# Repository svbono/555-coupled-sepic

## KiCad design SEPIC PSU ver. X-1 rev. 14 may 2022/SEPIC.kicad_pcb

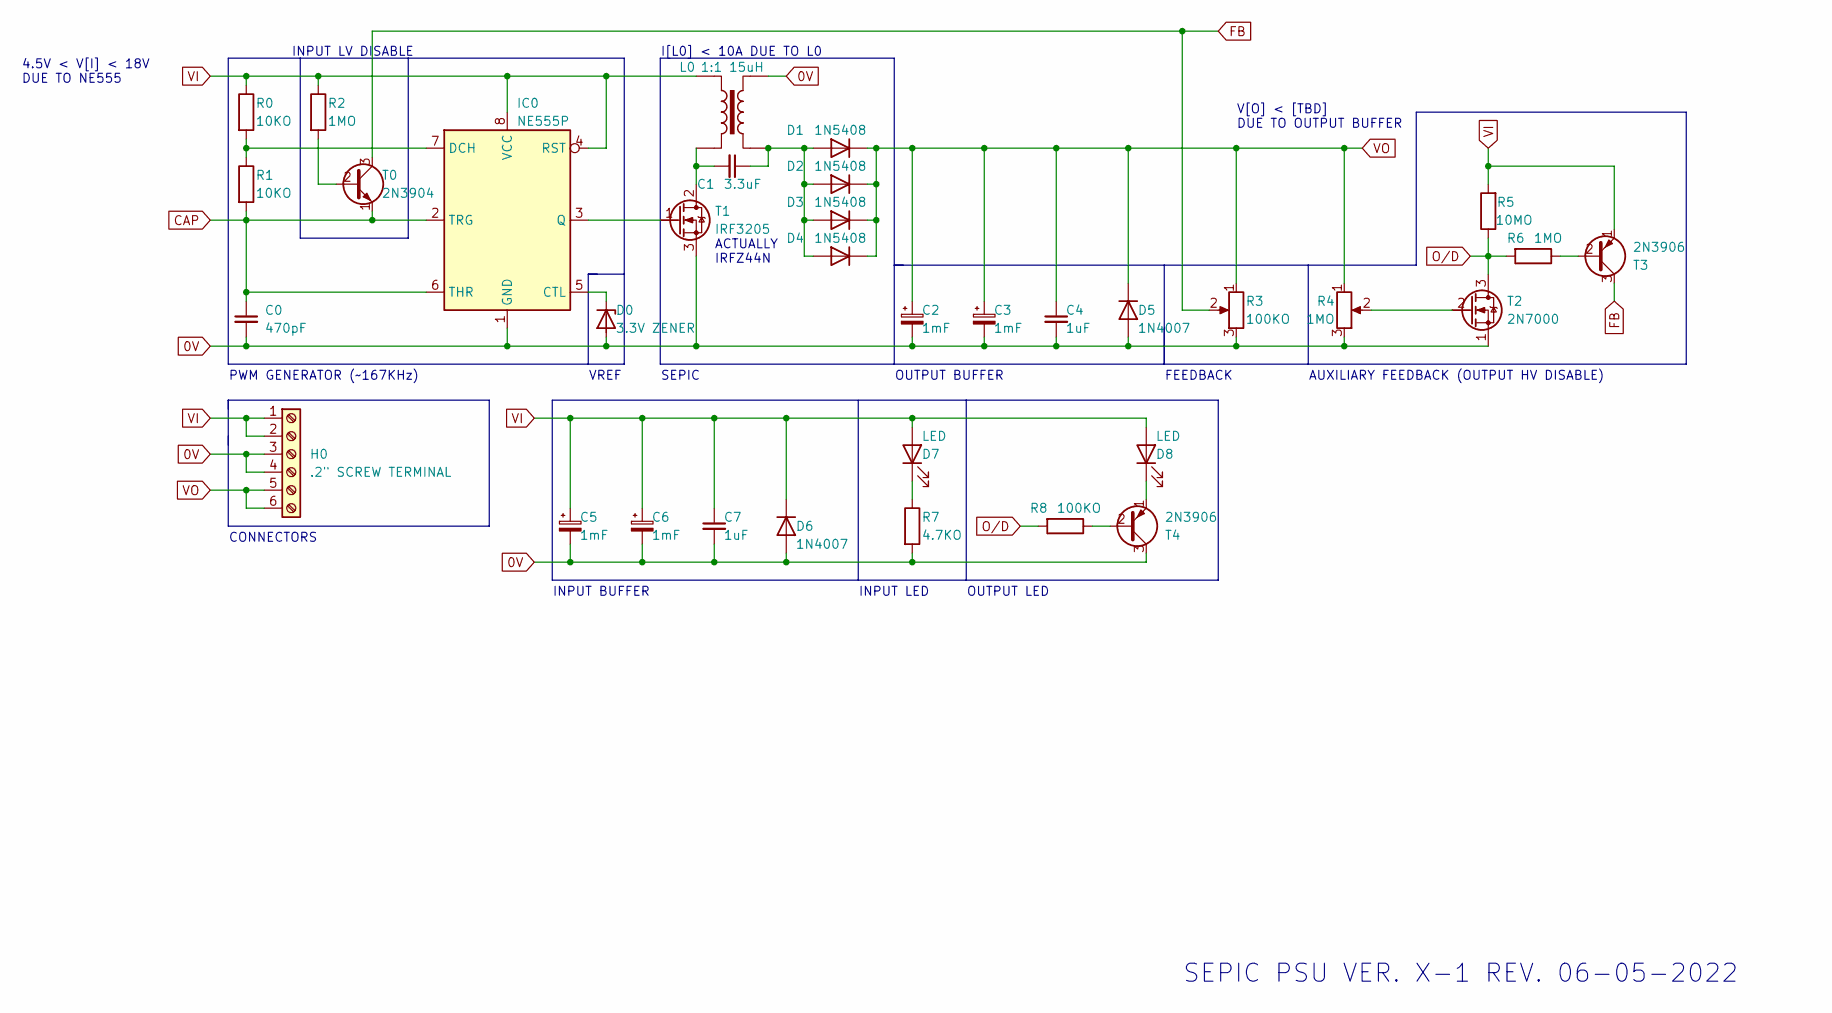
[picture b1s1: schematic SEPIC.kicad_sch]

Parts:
C0: 470pF; C_L.3in_W.1in_P.2in
C1: 3.3uF; C_L1.2in_W.4in_P1in
C2, C3, C5, C6: 1mF; C_Radial_D.6in_P.2in_P.3in
C4, C7: 1uF; C_L.3in_W.1in_P.2in
D0: 3.3V ZENER; D_L.4in_W.1in_P.3in
D1, D2, D3, D4: 1N5408; D_L.6in_W.2in_P.5in
D5, D6: 1N4007; D_L.4in_W.1in_P.3in
D7, D8: LED; LED_L.2in_W.1in_P.1in
H0: .2" SCREW TERMINAL; H_P.2in_6pin
IC0: NE555P; DIP-8_W7.62mm_Short
L0: 1:1 15uH; L_4pin_L1.2in_W.75in_Px1.1in_Py.55in_0
R0, R1: 10KO; R_L.4in_W.1in_P.3in
R2, R6: 1MO; R_L.4in_W.1in_P.3in
R3: 100KO; P_0
R4: 1MO; P_0
R5: 10MO; R_L.4in_W.1in_P.3in
R7: 4.7KO; R_L.4in_W.1in_P.3in
R8: 100KO; R_L.4in_W.1in_P.3in
T0: 2N3904; TO-92L_Inline_Wide
T1: IRF3205; TO-220-3_Horizontal_TabDown
T2: 2N7000; TO-92L_Inline_Wide
T3, T4: 2N3906; TO-92L_Inline_Wide

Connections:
0V: C0.2, C2.2, C3.2, C4.2, C5.2, C6.2, C7.2, D0.2 (A), D5.2 (A), D6.2 (A), H0.3, H0.4, IC0.1 (GND), L0.4, R3.3, R4.3, R7.2, T1.3 (S), T2.1 (S), T4.3 (C)
CAP: C0.1, IC0.2 (TRG), IC0.6 (THR), R1.2, T0.1 (E)
FB: R3.2, T0.3 (C), T3.3 (C)
unnamed: C1.1, D1.2 (A), D2.2 (A), D3.2 (A), D4.2 (A), L0.3
unnamed: C1.2, L0.2, T1.2 (D)
unnamed: D0.1 (K), IC0.5 (CTL)
unnamed: D7.1 (K), R7.1
unnamed: D8.1 (K), T4.1 (E)
unnamed: IC0.3 (Q), T1.1 (G)
unnamed: IC0.7 (DCH), R0.2, R1.1
unnamed: R2.2, T0.2 (B)
unnamed: R4.2, T2.2 (G)
unnamed: R6.1, T3.2 (B)
unnamed: R8.1, T4.2 (B)
O/D: R5.1, R6.2, R8.2, T2.3 (D)
VI: C5.1, C6.1, C7.1, D6.1 (K), D7.2 (A), D8.2 (A), H0.1, H0.2, IC0.4 (RST), IC0.8 (VCC), L0.1, R0.1, R2.1, R5.2, T3.1 (E)
VO: C2.1, C3.1, C4.1, D1.1 (K), D2.1 (K), D3.1 (K), D4.1 (K), D5.1 (K), H0.5, H0.6, R3.1, R4.1

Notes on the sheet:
FEEDBACK
SEPIC
CONNECTORS
SEPIC PSU VER. X-1 REV. 06-05-2022
INPUT LED
PWM GENERATOR (~167KHz)
INPUT BUFFER
OUTPUT BUFFER
VREF
INPUT LV DISABLE
OUTPUT LED
AUXILIARY FEEDBACK (OUTPUT HV DISABLE)
V[O] < [TBD] DUE TO OUTPUT BUFFER
I[L0] < 10A DUE TO L0
4.5V < V[I] < 18V DUE TO NE555
ACTUALLY IRFZ44N

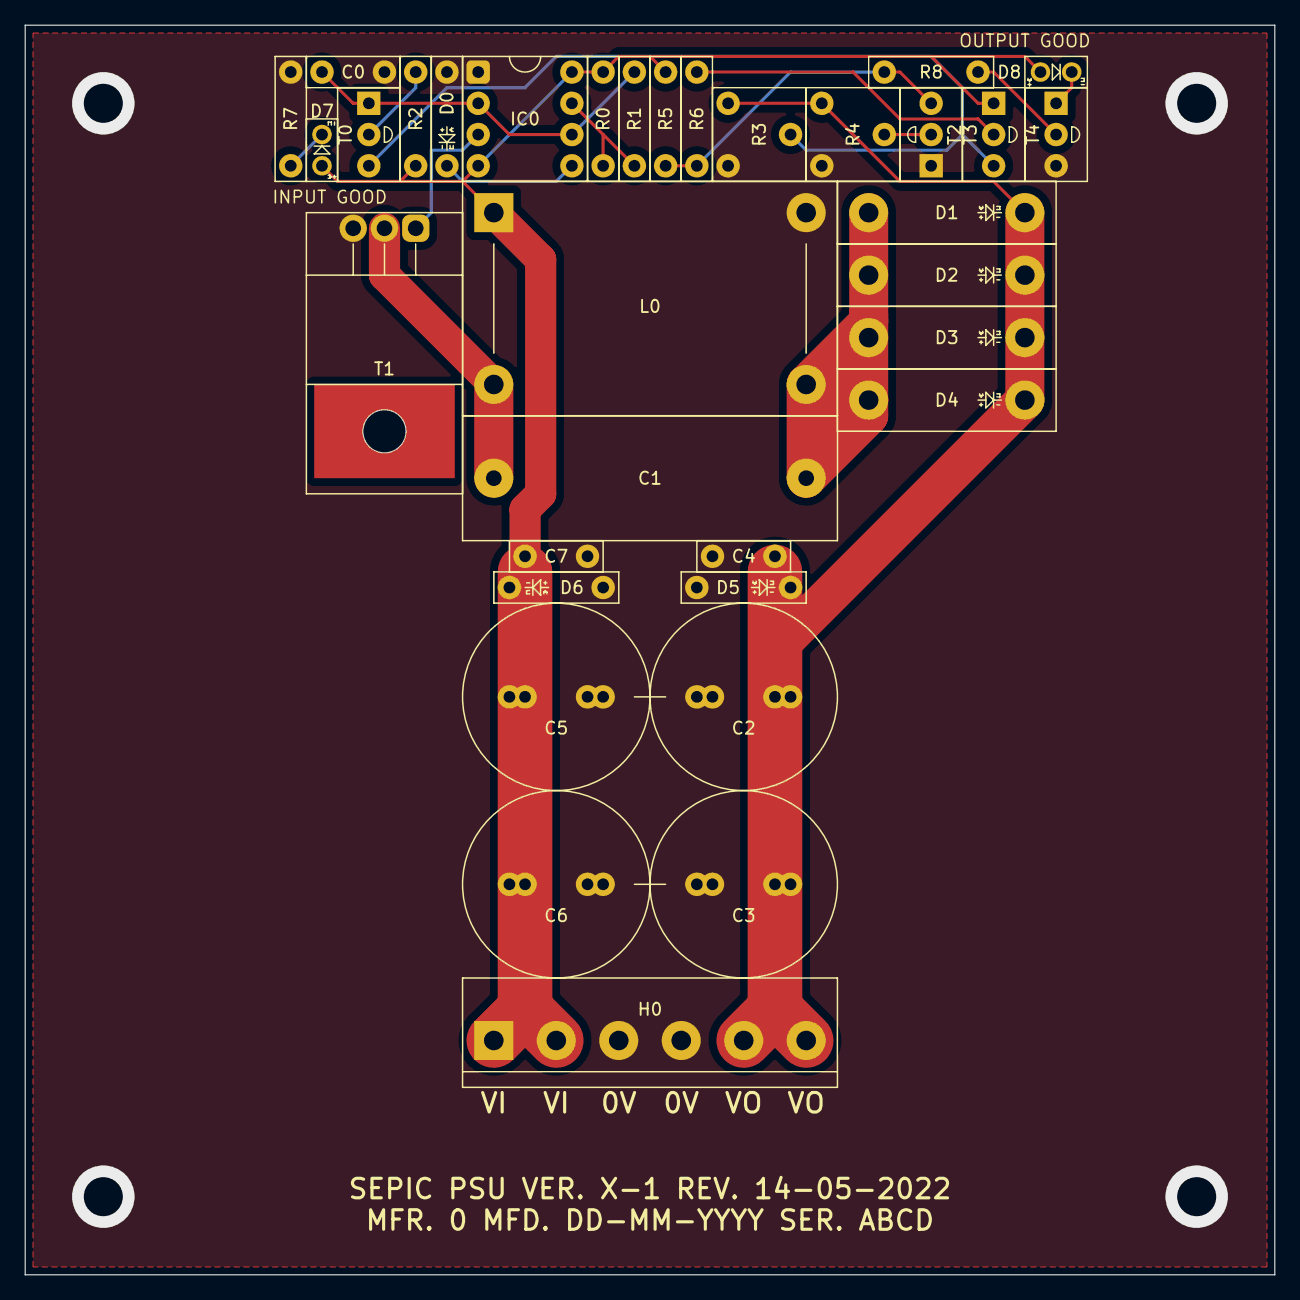
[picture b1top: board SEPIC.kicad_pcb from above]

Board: 2 copper layers, 101.6 x 101.6 mm, 34 parts (0 on the bottom side), 17 nets.

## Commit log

2023-06-01 Add files via upload
    Added everything except for the images.
2023-06-01 Add files via upload
    Added a photo of the first functioning rev. of the X-0.
2023-06-09 Delete SEPIC PSU ver. X-0 rev. 1 jun 2022/SEPIC-backups directory
    Deleted unnecessary backups.
2023-06-09 Delete SEPIC PSU ver. X-1 rev. 14 may 2022/SEPIC-backups directory
    Deleted unnecessary backups.
